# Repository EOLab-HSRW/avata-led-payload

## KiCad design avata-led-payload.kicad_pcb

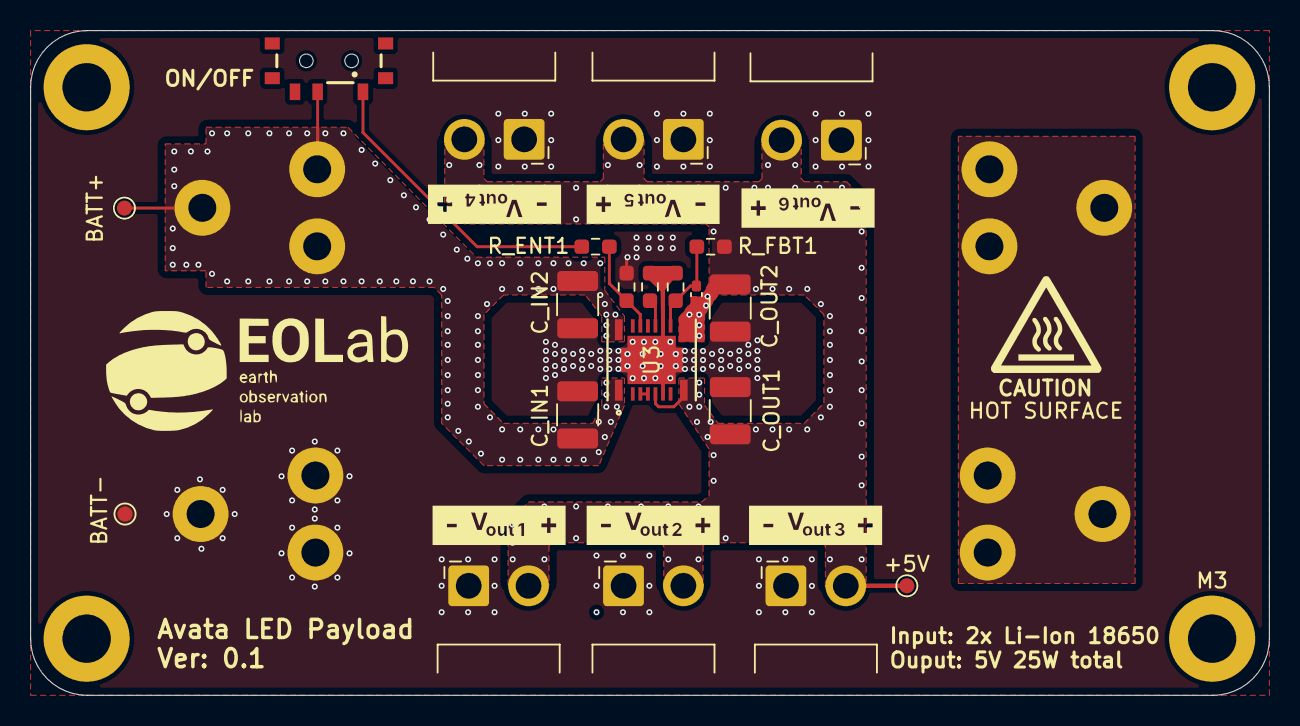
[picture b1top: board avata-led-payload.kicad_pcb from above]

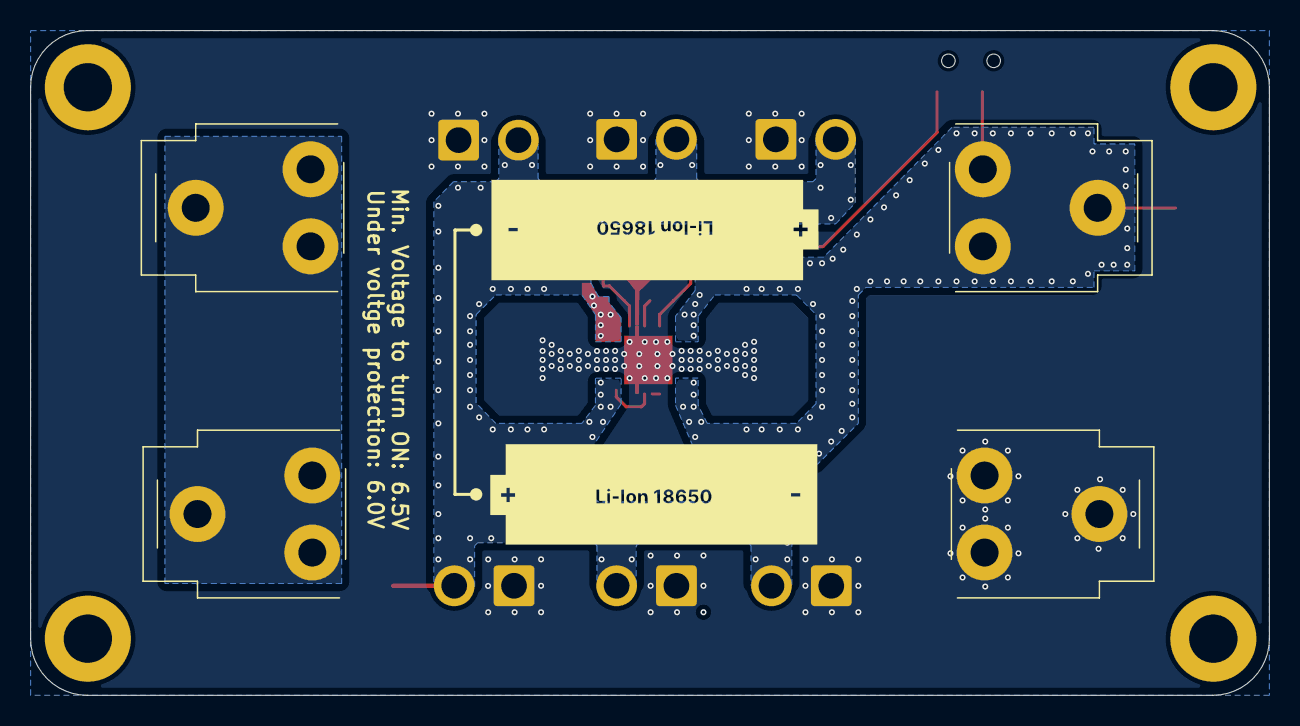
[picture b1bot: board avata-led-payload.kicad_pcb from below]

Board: 4 copper layers, 82.0 x 44.0 mm, 26 parts (2 on the bottom side), 10 nets.

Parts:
+5V: TestPoint; TestPoint_Pad_D1.0mm
BATT1, BATT2: -; BATT_18650_CLIP_HOLDER
BATT+: TestPoint; TestPoint_Pad_D1.0mm
BATT-: TestPoint; TestPoint_Pad_D1.0mm
C_FF1: 22pF; C_0402_1005Metric_Pad0.74x0.62mm_HandSolder
C_IN1, C_IN2: 10uF, 50V, X7R; C_1210_3225Metric_Pad1.33x2.70mm_HandSolder
C_OUT1, C_OUT2: 47uF, 10 V, X7R; C_1210_3225Metric_Pad1.33x2.70mm_HandSolder
M3: MountingHole_3.2mm_M3_ISO7380_Pad
NT1, NT2: NetTie_2; NetTie-2_SMD_Pad0.5mm
R_ENB1: 100k 1%; R_0603_1608Metric_Pad0.98x0.95mm_HandSolder
R_ENT1: 8.2k 1%; R_0603_1608Metric_Pad0.98x0.95mm_HandSolder
R_FBB1: 10k; R_0603_1608Metric_Pad0.98x0.95mm_HandSolder
R_FBT1: 40.2k; R_0603_1608Metric_Pad0.98x0.95mm_HandSolder
R_RT1: 13k; R_0603_1608Metric_Pad0.98x0.95mm_HandSolder
SW2: SW_DPDT_x2; 450404015514
U3: TLVM13660; B3QFN20_RDL_TEX
Vout1, Vout2, Vout3, Vout4, Vout5, Vout6: -; JST_VH_B2PS-VH_1x02_P3.96mm_Horizontal

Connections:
+5V: +5V.1, C_FF1.1, C_OUT1.1, C_OUT2.1, R_FBT1.1, U3.5 (VLDOIN), U3.8 (VOUT1), U3.9 (VOUT2), Vout1.2, Vout2.2, Vout3.2, Vout4.2, Vout5.2, Vout6.2
+BATT: BATT1.1, BATT+.1, C_IN1.1, C_IN2.1, SW2.2 (B), U3.1 (VIN1), U3.16 (VIN2)
/BATT_NET: BATT1.2, BATT2.1
/FB: C_FF1.2, R_FBB1.1, R_FBT1.2, U3.10 (FB)
/POWER_EN: R_ENB1.1, R_ENT1.2, U3.14 (EN)
/RBOOT: U3.3 (CBOOT), U3.4 (RBOOT)
/RT: R_RT1.1, U3.12 (RT)
/SW_EN: R_ENT1.1, SW2.1 (A)
AGND: NT1.2, NT2.2, R_FBB1.2, R_RT1.2, U3.6 (AGND), U3.11 (AGND)
PGND: BATT2.2, BATT-.1, C_IN1.2, C_IN2.2, C_OUT1.2, C_OUT2.2, NT1.1, NT2.1, R_ENB1.2, U3.17 (PGND), U3.18 (PGND), U3.19 (PGND), U3.20 (PGND), Vout1.1, Vout2.1, Vout3.1, Vout4.1, Vout5.1, Vout6.1

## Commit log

2025-01-13 init
